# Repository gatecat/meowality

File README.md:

# Meowality - Kria SoM mixed reality
 
 - Kria K26 SoM with UltraScale+ FPGA
     + 4x 1.5GHz Cortex A53
     + 4GB PS DDR4
     + 256k UltraScale+ logic cells;
     + hard H.264/H.265 IP
 - 2x LPM035M407B 1440x1600 90fps LCDs (2x4-lane MIPI DSI)
 - 2x 4-lane Pi cam connector intended for iMX477 (4k 60fps+)
 - 4-lane mini-Displayport connector on fabric GTH, up to HBR3/DP1.4
 - 2-lane M.2 connector for WiFi module on PS GTR
 - USB type-C connector with USB 2 PHY on PS MIO and USB 3 on PS GTR
 - USB PD power
 - ICM-20789 IMU
 - MMC5983 magnetometer
 - microSD card
 - 5x RGB LED
 - JTAG & UART on Harting 10B-1 connector

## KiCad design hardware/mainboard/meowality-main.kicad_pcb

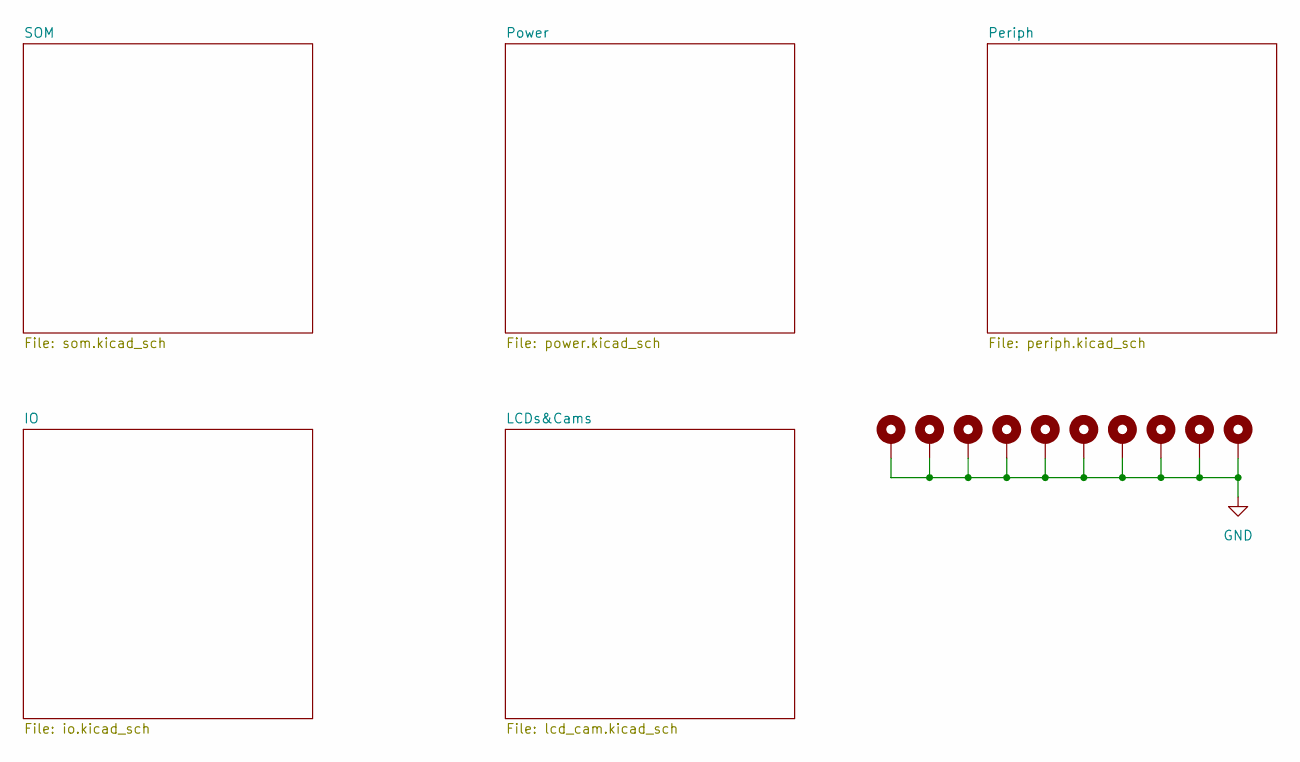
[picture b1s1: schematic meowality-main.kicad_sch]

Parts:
H1, H2, H3, H4, H5, H6, H7, H8, H9, H10: MountingHole_Pad; MountingHole_2.7mm_M2.5_Pad_Via

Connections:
GND: H1.1, H2.1, H3.1, H4.1, H5.1, H6.1, H7.1, H8.1, H9.1, H10.1; also elsewhere on the board

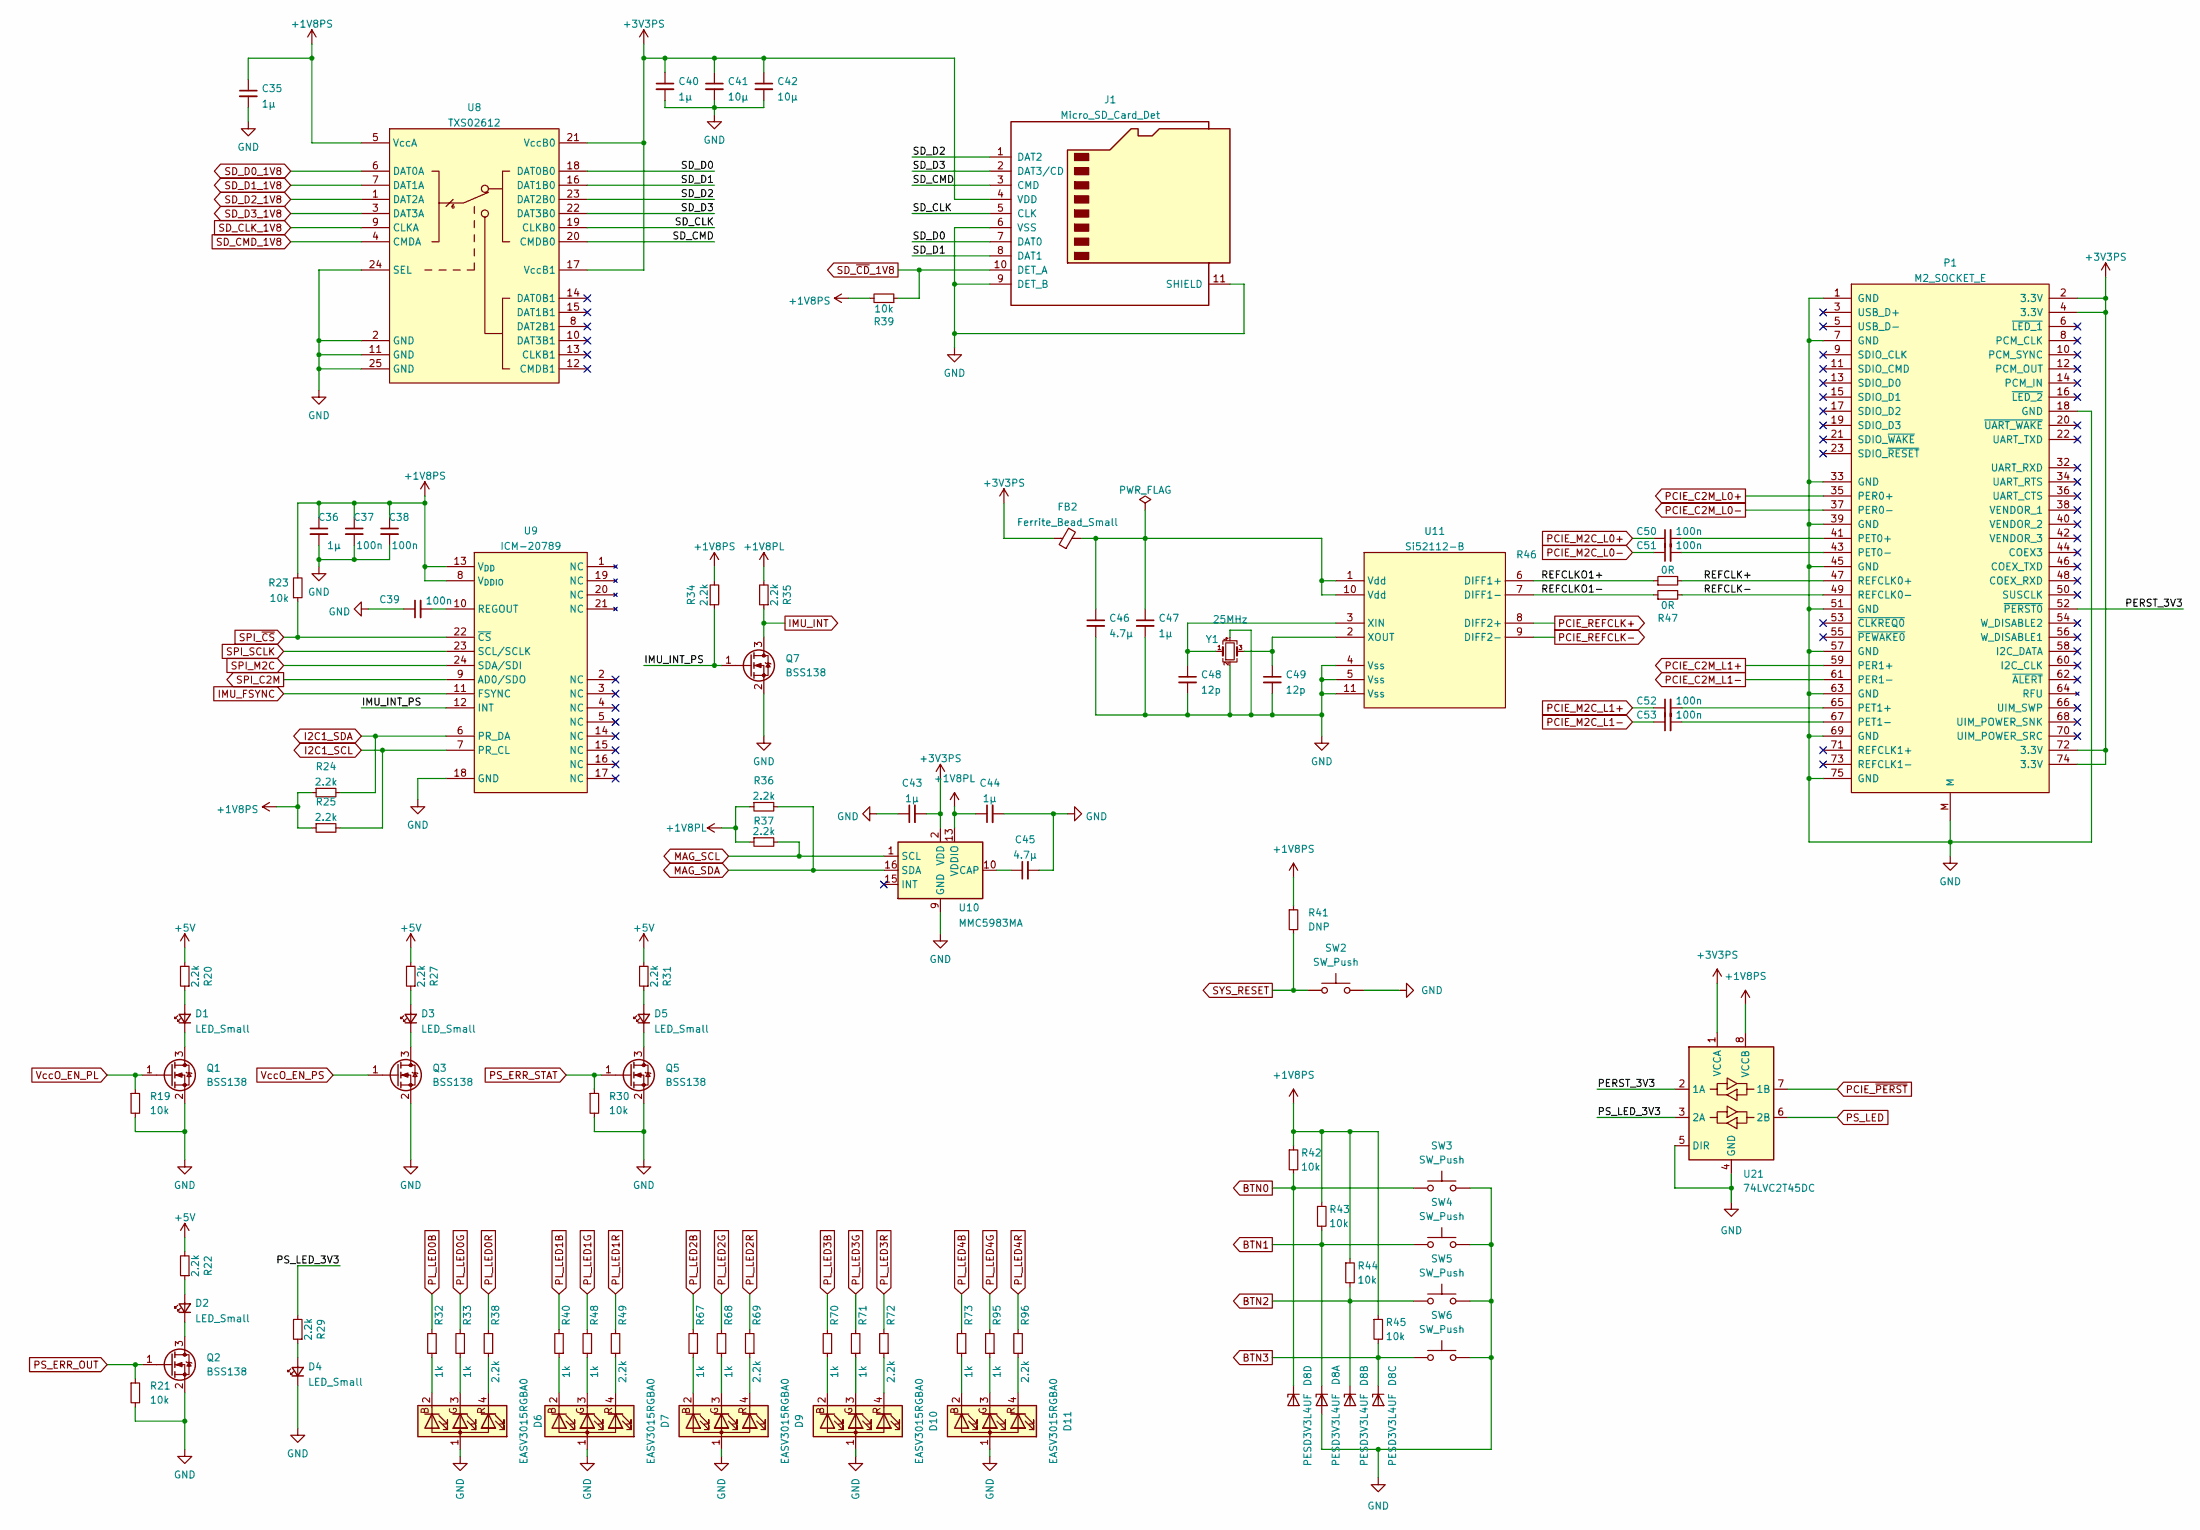
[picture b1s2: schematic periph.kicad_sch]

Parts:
C35, C36, C40, C43, C44, C47: 1µ; C_0603_1608Metric
C37, C38, C39, C50, C51, C52, C53: 100n; C_0402_1005Metric
C41, C42: 10µ; C_1206_3216Metric
C45, C46: 4.7µ; C_0603_1608Metric
C48, C49: 12p; C_0402_1005Metric
D1, D2, D3, D4, D5: LED_Small; LED_0603_1608Metric
D6, D7, D9, D10, D11: EASV3015RGBA0; EASV3015R
D8: PESD3V3L4UF; SOT-886
FB2: Ferrite_Bead_Small; L_0603_1608Metric
J1: Micro_SD_Card_Det; microSD_HC_Hirose_DM3AT-SF-PEJM5
P1: M2_SOCKET_E; 2199230-4
Q1, Q2, Q3, Q5, Q7: BSS138; SOT-23
R19, R21, R23, R30, R39, R42, R43, R44, R45: 10k; R_0402_1005Metric
R20, R22, R24, R25, R27, R29, R31, R34, R35, R36, R37, R38, R49, R69, R72, R96: 2.2k; R_0402_1005Metric
R32, R33, R40, R48, R67, R68, R70, R71, R73, R95: 1k; R_0402_1005Metric
R41: DNP; R_0402_1005Metric
R46, R47: 0R; R_0402_1005Metric
SW2, SW3, SW4, SW5, SW6: SW_Push; SW_SPST_B3S-1000
U8: TXS02612; WQFN-24-1EP_4x4mm_P0.5mm_EP2.45x2.45mm
U9: ICM-20789; InvenSense_QFN-24_4x4mm_P0.5mm
U10: MMC5983MA; LGA-16_3x3mm_P0.5mm
U11: Si52112-B; TDFN10_3x3mm_p0.5mm
U21: 74LVC2T45DC; X2SON-8_1.4x1mm_P0.35mm
Y1: 25MHz; Crystal_SMD_3225-4Pin_3.2x2.5mm

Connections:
+1V8PL: C44.1, R35.2, R36.1, R37.1, U10.13 (VDDIO); also elsewhere on the board
+1V8PS: C35.1, C36.1, C37.1, C38.1, R23.2, R24.1, R25.1, R34.2, R39.2, R41.1, R42.1, R43.1, R44.1, R45.1, U8.5 (VccA), U9.8 (V_{DDIO}), U9.13 (V_{DD}), U21.8 (VCCB); also elsewhere on the board
+3V3PS: C40.1, C41.1, C42.1, C43.2, FB2.1, J1.4 (VDD), P1.2 (3.3V), P1.4 (3.3V), P1.72 (3.3V), P1.74 (3.3V), U8.17 (VccB1), U8.21 (VccB0), U10.2 (VDD), U21.1 (VCCA); also elsewhere on the board
+5V: R20.2, R22.2, R27.2, R31.2; also elsewhere on the board
/Periph/IMU_INT_PS: Q7.1 (G), R34.1, U9.12 (INT)
/Periph/PERST_3V3: P1.52 (~PERST0), U21.2 (1A)
/Periph/PS_LED_3V3: R29.2, U21.3 (2A)
/Periph/REFCLK+: P1.47 (REFCLK0+), R46.2
/Periph/REFCLK-: P1.49 (REFCLK0-), R47.2
/Periph/REFCLKO1+: R46.1, U11.6 (DIFF1+)
/Periph/REFCLKO1-: R47.1, U11.7 (DIFF1-)
/Periph/SD_CLK: J1.5 (CLK), U8.19 (CLKB0)
/Periph/SD_CMD: J1.3 (CMD), U8.20 (CMDB0)
/Periph/SD_D0: J1.7 (DAT0), U8.18 (DAT0B0)
/Periph/SD_D1: J1.8 (DAT1), U8.16 (DAT1B0)
/Periph/SD_D2: J1.1 (DAT2), U8.23 (DAT2B0)
/Periph/SD_D3: J1.2 (DAT3/CD), U8.22 (DAT3B0)
BTN0: D8.6 (K4), R42.2, SW3.1; also elsewhere on the board
BTN1: D8.1 (K1), R43.2, SW4.1; also elsewhere on the board
BTN2: D8.3 (K2), R44.2, SW5.1; also elsewhere on the board
BTN3: D8.4 (K3), R45.2, SW6.1; also elsewhere on the board
GND: C35.2, C36.2, C37.2, C38.2, C39.1, C40.2, C41.2, C42.2, C43.1, C44.2, C45.2, C46.2, C47.2, C48.2, C49.2, D4.1 (K), D6.1 (A), D7.1 (A), D8.2 (A), D8.5 (A), D9.1 (A), D10.1 (A), D11.1 (A), J1.6 (VSS), J1.9 (DET_B), J1.11 (SHIELD), P1.1 (GND), P1.7 (GND), P1.18 (GND), P1.33 (GND), P1.39 (GND), P1.45 (GND), P1.51 (GND), P1.57 (GND), P1.63 (GND), P1.69 (GND), P1.75 (GND), P1.M, Q1.2 (S), Q2.2 (S), Q3.2 (S), Q5.2 (S), Q7.2 (S), R19.2, R21.2, R30.2, SW2.2, SW3.2, SW4.2, SW5.2, SW6.2, U8.2 (GND), U8.11 (GND), U8.24 (SEL), U8.25 (GND), U9.18 (GND), U10.9 (GND), U10.11 (GND), U11.4 (Vss), U11.5 (Vss), U11.11 (Vss), U21.4 (GND), U21.5 (DIR), Y1.2, Y1.4; also elsewhere on the board
I2C1_SCL: R25.2, U9.7 (PR_CL); also elsewhere on the board
I2C1_SDA: R24.2, U9.6 (PR_DA); also elsewhere on the board
IMU_FSYNC: U9.11 (FSYNC); also elsewhere on the board
IMU_INT: Q7.3 (D), R35.1; also elsewhere on the board
MAG_SCL: R37.2, U10.1 (SCL); also elsewhere on the board
MAG_SDA: R36.2, U10.16 (SDA); also elsewhere on the board
unnamed: C39.2, U9.10 (REGOUT)
unnamed: C45.1, U10.10 (CAP)
unnamed: C46.1, C47.1, FB2.2, U11.1 (Vdd), U11.10 (Vdd)
unnamed: C48.1, U11.3 (XIN), Y1.1
unnamed: C49.1, U11.2 (XOUT), Y1.3
unnamed: C50.2, P1.41 (PET0+)
unnamed: C51.2, P1.43 (PET0-)
unnamed: C52.2, P1.65 (PET1+)
unnamed: C53.2, P1.67 (PET1-)
unnamed: D1.1 (K), Q1.3 (D)
unnamed: D1.2 (A), R20.1
unnamed: D2.1 (K), Q2.3 (D)
unnamed: D2.2 (A), R22.1
unnamed: D3.1 (K), Q3.3 (D)
unnamed: D3.2 (A), R27.1
unnamed: D4.2 (A), R29.1
unnamed: D5.1 (K), Q5.3 (D)
unnamed: D5.2 (A), R31.1
unnamed: D6.2 (BK), R32.1
unnamed: D6.3 (GK), R33.1
unnamed: D6.4 (RK), R38.1
unnamed: D7.2 (BK), R40.1
unnamed: D7.3 (GK), R48.1
unnamed: D7.4 (RK), R49.1
unnamed: D9.2 (BK), R67.1
unnamed: D9.3 (GK), R68.1
unnamed: D9.4 (RK), R69.1
unnamed: D10.2 (BK), R70.1
unnamed: D10.3 (GK), R71.1
unnamed: D10.4 (RK), R72.1
unnamed: D11.2 (BK), R73.1
unnamed: D11.3 (GK), R95.1
unnamed: D11.4 (RK), R96.1
PCIE_C2M_L0+: P1.35 (PER0+); also elsewhere on the board
PCIE_C2M_L0-: P1.37 (PER0-); also elsewhere on the board
PCIE_C2M_L1+: P1.59 (PER1+); also elsewhere on the board
PCIE_C2M_L1-: P1.61 (PER1-); also elsewhere on the board
PCIE_M2C_L0+: C50.1; also elsewhere on the board
PCIE_M2C_L0-: C51.1; also elsewhere on the board
PCIE_M2C_L1+: C52.1; also elsewhere on the board
PCIE_M2C_L1-: C53.1; also elsewhere on the board
PCIE_REFCLK+: U11.8 (DIFF2+); also elsewhere on the board
PCIE_REFCLK-: U11.9 (DIFF2-); also elsewhere on the board
PCIE_~PERST: U21.7 (1B); also elsewhere on the board
PL_LED0B: R32.2; also elsewhere on the board
PL_LED0G: R33.2; also elsewhere on the board
PL_LED0R: R38.2; also elsewhere on the board
PL_LED1B: R40.2; also elsewhere on the board
PL_LED1G: R48.2; also elsewhere on the board
PL_LED1R: R49.2; also elsewhere on the board
PL_LED2B: R67.2; also elsewhere on the board
PL_LED2G: R68.2; also elsewhere on the board
PL_LED2R: R69.2; also elsewhere on the board
PL_LED3B: R70.2; also elsewhere on the board
PL_LED3G: R71.2; also elsewhere on the board
PL_LED3R: R72.2; also elsewhere on the board
PL_LED4B: R73.2; also elsewhere on the board
PL_LED4G: R95.2; also elsewhere on the board
PL_LED4R: R96.2; also elsewhere on the board
PS_ERR_OUT: Q2.1 (G), R21.1; also elsewhere on the board
PS_ERR_STAT: Q5.1 (G), R30.1; also elsewhere on the board
PS_LED: U21.6 (2B); also elsewhere on the board
SD_CLK_1V8: U8.9 (CLKA); also elsewhere on the board
SD_CMD_1V8: U8.4 (CMDA); also elsewhere on the board
SD_D0_1V8: U8.6 (DAT0A); also elsewhere on the board
SD_D1_1V8: U8.7 (DAT1A); also elsewhere on the board
SD_D2_1V8: U8.1 (DAT2A); also elsewhere on the board
SD_D3_1V8: U8.3 (DAT3A); also elsewhere on the board
SD_~CD_1V8: J1.10 (DET_A), R39.1; also elsewhere on the board
SPI_C2M: U9.9 (AD0/SDO); also elsewhere on the board
SPI_M2C: U9.24 (SDA/SDI); also elsewhere on the board
SPI_SCLK: U9.23 (SCL/SCLK); also elsewhere on the board
SPI_~CS: R23.1, U9.22 (~CS); also elsewhere on the board
SYS_RESET: R41.2, SW2.1; also elsewhere on the board
VccO_EN_PL: Q1.1 (G), R19.1; also elsewhere on the board
VccO_EN_PS: Q3.1 (G); also elsewhere on the board

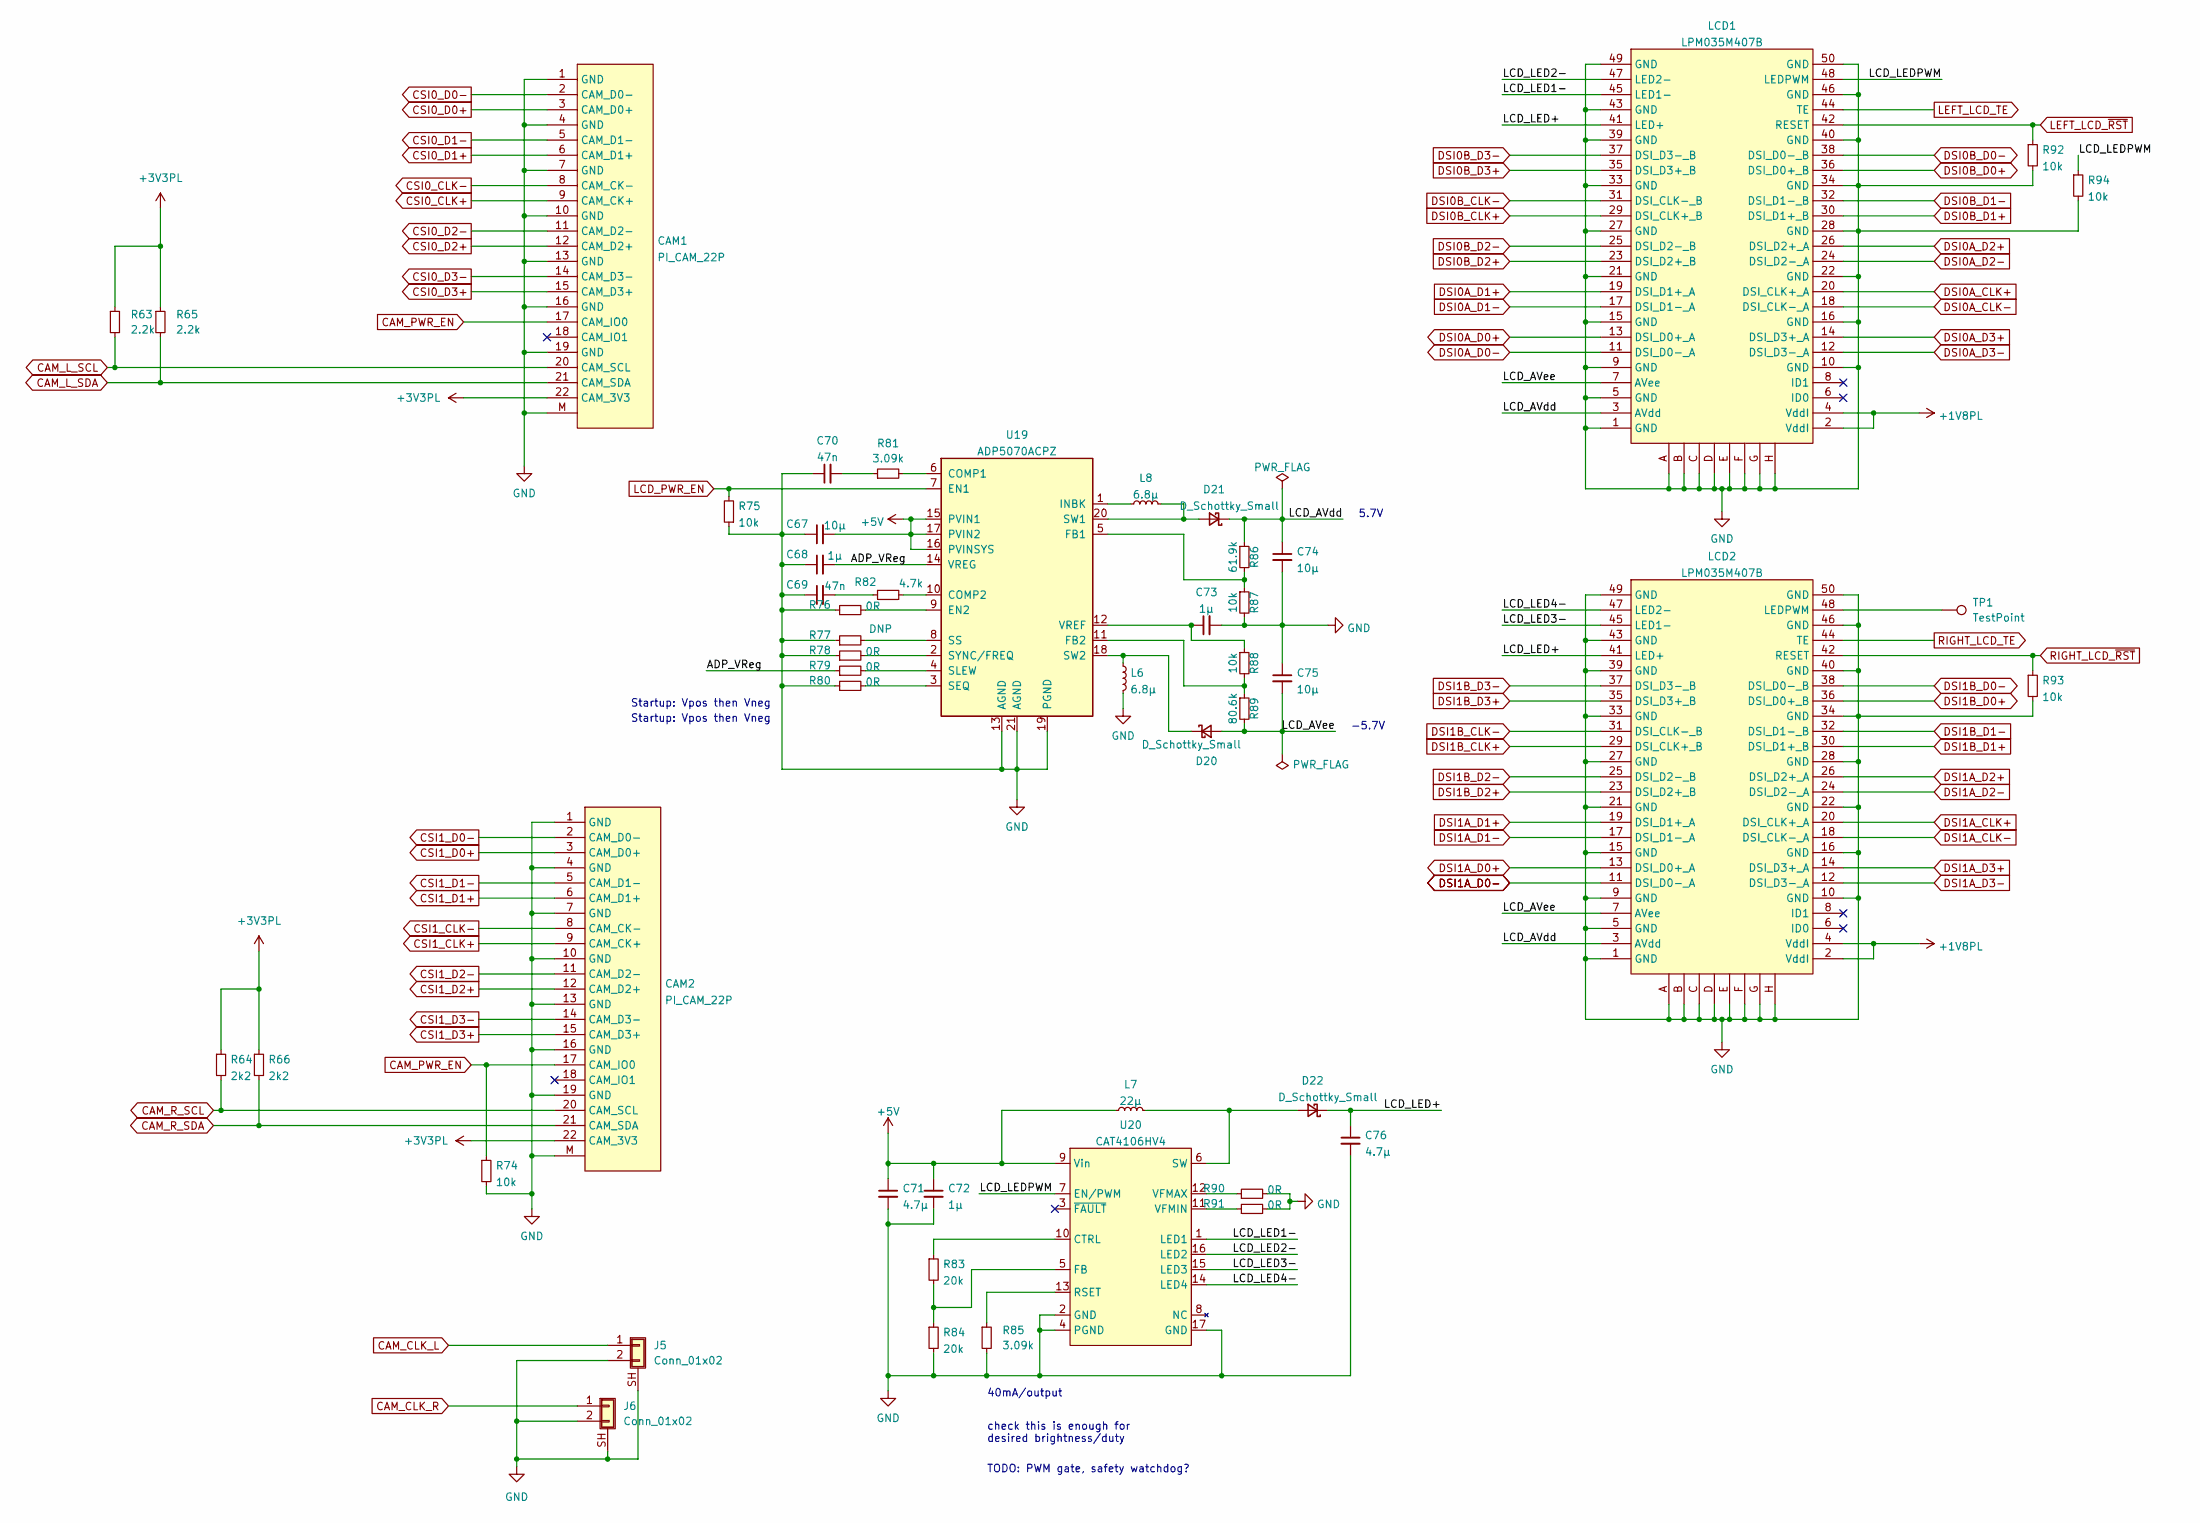
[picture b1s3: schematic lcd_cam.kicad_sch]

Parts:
C67, C74, C75: 10µ; C_1206_3216Metric
C68, C72, C73: 1µ; C_0603_1608Metric
C69, C70: 47n; C_0402_1005Metric
C71, C76: 4.7µ; C_0603_1608Metric
CAM1, CAM2: PI_CAM_22P; 54548-2271
D20, D21, D22: D_Schottky_Small; D_SMA
J5, J6: Conn_01x02; TE-292227-2
L6, L8: 6.8µ; L_Taiyo-Yuden_NR-50xx
L7: 22µ; L_Taiyo-Yuden_NR-50xx
LCD1, LCD2: LPM035M407B; 245863060104829
R63, R65: 2.2k; R_0402_1005Metric
R64, R66: 2k2; R_0402_1005Metric
R74, R75, R87, R88, R92, R93, R94: 10k; R_0402_1005Metric
R76, R78, R79, R80, R90, R91: 0R; R_0402_1005Metric
R77: DNP; R_0402_1005Metric
R81, R85: 3.09k; R_0402_1005Metric
R82: 4.7k; R_0402_1005Metric
R83, R84: 20k; R_0402_1005Metric
R86: 61.9k; R_0402_1005Metric
R89: 80.6k; R_0402_1005Metric
TP1: TestPoint; TestPoint_Pad_D2.0mm
U19: ADP5070ACPZ; QFN-20-1EP_4x4mm_P0.5mm_EP2.6x2.6mm
U20: CAT4106HV4; QFN-16-1EP_4x4mm_P0.65mm_EP2.1x2.1mm

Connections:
+1V8PL: LCD1.2 (VddI), LCD1.4 (VddI), LCD2.2 (VddI), LCD2.4 (VddI); also elsewhere on the board
+3V3PL: CAM1.22 (CAM_3V3), CAM2.22 (CAM_3V3), R63.1, R64.1, R65.1, R66.1; also elsewhere on the board
+5V: C67.2, C71.1, C72.1, L7.1, U19.15 (PVIN1), U19.16 (PVINSYS), U19.17 (PVIN2), U20.9 (Vin); also elsewhere on the board
/LCDs&Cams/ADP_VReg: C68.2, R79.1, U19.14 (VREG)
/LCDs&Cams/LCD_AVdd: C74.1, D21.1 (K), LCD1.3 (AVdd), LCD2.3 (AVdd), R86.1
/LCDs&Cams/LCD_AVee: C75.2, D20.2 (A), LCD1.7 (AVee), LCD2.7 (AVee), R89.2
/LCDs&Cams/LCD_LED1-: LCD1.45 (LED1-), U20.1 (LED1)
/LCDs&Cams/LCD_LED2-: LCD1.47 (LED2-), U20.16 (LED2)
/LCDs&Cams/LCD_LED3-: LCD2.45 (LED1-), U20.15 (LED3)
/LCDs&Cams/LCD_LED4-: LCD2.47 (LED2-), U20.14 (LED4)
/LCDs&Cams/LCD_LED+: C76.1, D22.1 (K), LCD1.41 (LED+), LCD2.41 (LED+)
/LCDs&Cams/LCD_LEDPWM: LCD1.48 (LEDPWM), R94.1, U20.7 (EN/PWM)
CAM_CLK_L: J5.1; also elsewhere on the board
CAM_CLK_R: J6.1; also elsewhere on the board
CAM_L_SCL: CAM1.20 (CAM_SCL), R63.2; also elsewhere on the board
CAM_L_SDA: CAM1.21 (CAM_SDA), R65.2; also elsewhere on the board
CAM_PWR_EN: CAM1.17 (CAM_IO0), CAM2.17 (CAM_IO0), R74.1; also elsewhere on the board
CAM_R_SCL: CAM2.20 (CAM_SCL), R64.2; also elsewhere on the board
CAM_R_SDA: CAM2.21 (CAM_SDA), R66.2; also elsewhere on the board
CSI0_CLK+: CAM1.9 (CAM_CK+); also elsewhere on the board
CSI0_CLK-: CAM1.8 (CAM_CK-); also elsewhere on the board
CSI0_D0+: CAM1.3 (CAM_D0+); also elsewhere on the board
CSI0_D0-: CAM1.2 (CAM_D0-); also elsewhere on the board
CSI0_D1+: CAM1.6 (CAM_D1+); also elsewhere on the board
CSI0_D1-: CAM1.5 (CAM_D1-); also elsewhere on the board
CSI0_D2+: CAM1.12 (CAM_D2+); also elsewhere on the board
CSI0_D2-: CAM1.11 (CAM_D2-); also elsewhere on the board
CSI0_D3+: CAM1.15 (CAM_D3+); also elsewhere on the board
CSI0_D3-: CAM1.14 (CAM_D3-); also elsewhere on the board
CSI1_CLK+: CAM2.9 (CAM_CK+); also elsewhere on the board
CSI1_CLK-: CAM2.8 (CAM_CK-); also elsewhere on the board
CSI1_D0+: CAM2.3 (CAM_D0+); also elsewhere on the board
CSI1_D0-: CAM2.2 (CAM_D0-); also elsewhere on the board
CSI1_D1+: CAM2.6 (CAM_D1+); also elsewhere on the board
CSI1_D1-: CAM2.5 (CAM_D1-); also elsewhere on the board
CSI1_D2+: CAM2.12 (CAM_D2+); also elsewhere on the board
CSI1_D2-: CAM2.11 (CAM_D2-); also elsewhere on the board
CSI1_D3+: CAM2.15 (CAM_D3+); also elsewhere on the board
CSI1_D3-: CAM2.14 (CAM_D3-); also elsewhere on the board
DSI0A_CLK+: LCD1.20 (DSI_CLK+_A); also elsewhere on the board
DSI0A_CLK-: LCD1.18 (DSI_CLK-_A); also elsewhere on the board
DSI0A_D0+: LCD1.13 (DSI_D0+_A); also elsewhere on the board
DSI0A_D0-: LCD1.11 (DSI_D0-_A); also elsewhere on the board
DSI0A_D1+: LCD1.19 (DSI_D1+_A); also elsewhere on the board
DSI0A_D1-: LCD1.17 (DSI_D1-_A); also elsewhere on the board
DSI0A_D2+: LCD1.26 (DSI_D2+_A); also elsewhere on the board
DSI0A_D2-: LCD1.24 (DSI_D2-_A); also elsewhere on the board
DSI0A_D3+: LCD1.14 (DSI_D3+_A); also elsewhere on the board
DSI0A_D3-: LCD1.12 (DSI_D3-_A); also elsewhere on the board
DSI0B_CLK+: LCD1.29 (DSI_CLK+_B); also elsewhere on the board
DSI0B_CLK-: LCD1.31 (DSI_CLK-_B); also elsewhere on the board
DSI0B_D0+: LCD1.36 (DSI_D0+_B); also elsewhere on the board
DSI0B_D0-: LCD1.38 (DSI_D0-_B); also elsewhere on the board
DSI0B_D1+: LCD1.30 (DSI_D1+_B); also elsewhere on the board
DSI0B_D1-: LCD1.32 (DSI_D1-_B); also elsewhere on the board
DSI0B_D2+: LCD1.23 (DSI_D2+_B); also elsewhere on the board
DSI0B_D2-: LCD1.25 (DSI_D2-_B); also elsewhere on the board
DSI0B_D3+: LCD1.35 (DSI_D3+_B); also elsewhere on the board
DSI0B_D3-: LCD1.37 (DSI_D3-_B); also elsewhere on the board
DSI1A_CLK+: LCD2.20 (DSI_CLK+_A); also elsewhere on the board
DSI1A_CLK-: LCD2.18 (DSI_CLK-_A); also elsewhere on the board
DSI1A_D0+: LCD2.13 (DSI_D0+_A); also elsewhere on the board
DSI1A_D0-: LCD2.11 (DSI_D0-_A); also elsewhere on the board
DSI1A_D1+: LCD2.19 (DSI_D1+_A); also elsewhere on the board
DSI1A_D1-: LCD2.17 (DSI_D1-_A); also elsewhere on the board
DSI1A_D2+: LCD2.26 (DSI_D2+_A); also elsewhere on the board
DSI1A_D2-: LCD2.24 (DSI_D2-_A); also elsewhere on the board
DSI1A_D3+: LCD2.14 (DSI_D3+_A); also elsewhere on the board
DSI1A_D3-: LCD2.12 (DSI_D3-_A); also elsewhere on the board
DSI1B_CLK+: LCD2.29 (DSI_CLK+_B); also elsewhere on the board
DSI1B_CLK-: LCD2.31 (DSI_CLK-_B); also elsewhere on the board
DSI1B_D0+: LCD2.36 (DSI_D0+_B); also elsewhere on the board
DSI1B_D0-: LCD2.38 (DSI_D0-_B); also elsewhere on the board
DSI1B_D1+: LCD2.30 (DSI_D1+_B); also elsewhere on the board
DSI1B_D1-: LCD2.32 (DSI_D1-_B); also elsewhere on the board
DSI1B_D2+: LCD2.23 (DSI_D2+_B); also elsewhere on the board
DSI1B_D2-: LCD2.25 (DSI_D2-_B); also elsewhere on the board
DSI1B_D3+: LCD2.35 (DSI_D3+_B); also elsewhere on the board
DSI1B_D3-: LCD2.37 (DSI_D3-_B); also elsewhere on the board
GND: C67.1, C68.1, C69.1, C70.1, C71.2, C72.2, C73.2, C74.2, C75.1, C76.2, CAM1.1 (GND), CAM1.4 (GND), CAM1.7 (GND), CAM1.10 (GND), CAM1.13 (GND), CAM1.16 (GND), CAM1.19 (GND), CAM1.M, CAM2.1 (GND), CAM2.4 (GND), CAM2.7 (GND), CAM2.10 (GND), CAM2.13 (GND), CAM2.16 (GND), CAM2.19 (GND), CAM2.M, J5.2, J5.SH (Shield), J6.2, J6.SH (Shield), L6.2, LCD1.1 (GND), LCD1.5 (GND), LCD1.9 (GND), LCD1.10 (GND), LCD1.15 (GND), LCD1.16 (GND), LCD1.21 (GND), LCD1.22 (GND), LCD1.27 (GND), LCD1.28 (GND), LCD1.33 (GND), LCD1.34 (GND), LCD1.39 (GND), LCD1.40 (GND), LCD1.43 (GND), LCD1.46 (GND), LCD1.49 (GND), LCD1.50 (GND), LCD1.A, LCD1.B, LCD1.C, LCD1.D, LCD1.E, LCD1.F, LCD1.G, LCD1.H, LCD2.1 (GND), LCD2.5 (GND), LCD2.9 (GND), LCD2.10 (GND), LCD2.15 (GND), LCD2.16 (GND), LCD2.21 (GND), LCD2.22 (GND), LCD2.27 (GND), LCD2.28 (GND), LCD2.33 (GND), LCD2.34 (GND), LCD2.39 (GND), LCD2.40 (GND), LCD2.43 (GND), LCD2.46 (GND), LCD2.49 (GND), LCD2.50 (GND), LCD2.A, LCD2.B, LCD2.C, LCD2.D, LCD2.E, LCD2.F, LCD2.G, LCD2.H, R74.2, R75.1, R76.1, R77.1, R78.1, R80.1, R84.2, R85.2, R87.2, R90.2, R91.2, R92.2, R93.2, R94.2, U19.13 (AGND), U19.19 (PGND), U19.21 (AGND), U20.2 (GND), U20.4 (PGND), U20.17 (GND); also elsewhere on the board
LCD_PWR_EN: R75.2, U19.7 (EN1); also elsewhere on the board
LEFT_LCD_TE: LCD1.44 (TE); also elsewhere on the board
LEFT_LCD_~RST: LCD1.42 (RESET), R92.1; also elsewhere on the board
unnamed: C69.2, R82.1
unnamed: C70.2, R81.1
unnamed: C73.1, R88.1, U19.12 (VREF)
unnamed: D20.1 (K), L6.1, U19.18 (SW2)
unnamed: D21.2 (A), L8.2, U19.20 (SW1)
unnamed: D22.2 (A), L7.2, U20.6 (SW)
unnamed: L8.1, U19.1 (INBK)
unnamed: LCD2.48 (LEDPWM), TP1.1
unnamed: R76.2, U19.9 (EN2)
unnamed: R77.2, U19.8 (SS)
unnamed: R78.2, U19.2 (SYNC/FREQ)
unnamed: R79.2, U19.4 (SLEW)
unnamed: R80.2, U19.3 (SEQ)
unnamed: R81.2, U19.6 (COMP1)
unnamed: R82.2, U19.10 (COMP2)
unnamed: R83.1, U20.10 (CTRL)
unnamed: R83.2, R84.1, U20.5 (FB)
unnamed: R85.1, U20.13 (RSET)
unnamed: R86.2, R87.1, U19.5 (FB1)
unnamed: R88.2, R89.1, U19.11 (FB2)
unnamed: R90.1, U20.12 (VFMAX)
unnamed: R91.1, U20.11 (VFMIN)
RIGHT_LCD_TE: LCD2.44 (TE); also elsewhere on the board
RIGHT_LCD_~RST: LCD2.42 (RESET), R93.1; also elsewhere on the board

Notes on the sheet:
40mA/output
TODO: PWM gate, safety watchdog?
check this is enough for desired brightness/duty
5.7V
Startup: Vpos then Vneg
-5.7V
